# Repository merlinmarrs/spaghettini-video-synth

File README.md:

# spaghettini-video-synth

This simple kit was developed with funding from La Diagonale UP Saclay and the CVEC programme :

"Arduino Coding and Video Synthesis Workshop

Lean to code in C with Arduino, solder and assemble a custom printed-circuit board made in the Fablab, and make your own algorithmically-generated video art!

This workshop is inspired by the improvisational music of Live coding (https://fr.wikipedia.org/wiki/Live_coding) and the burgeoning minimalist Bytebeats movement (https://nightmachines.tv/bytebeats-tutorial).

Our video synthesis kit plugs in to the Arduino (https://www.arduino.cc/), a reprogrammable embedded micro-controller that can interact with the world through code, and uses the VGAX library (https://github.com/smaffer/vgax) to generate funky video.

Meet other creative technologists and sharpen your expertise in computer sciences and electronics soldering!"

**Thank you to Anna Offenwanger for the code !

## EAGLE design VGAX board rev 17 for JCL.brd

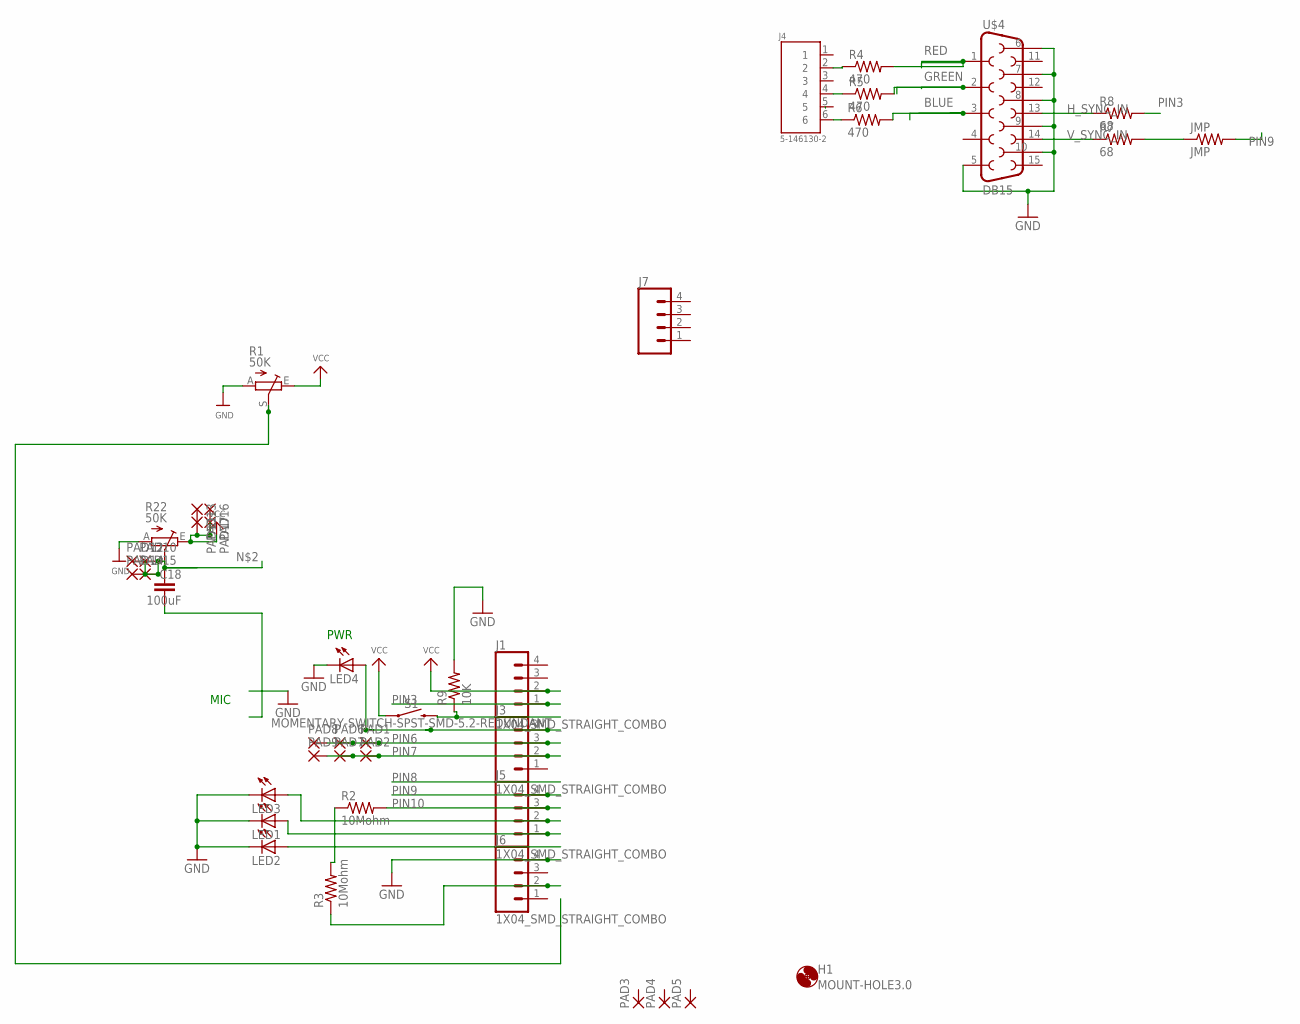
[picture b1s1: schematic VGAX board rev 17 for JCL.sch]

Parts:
C18: 100uF; 1206
H1: MOUNT-HOLE3.0; 3,0
J1, J3, J5, J6, J7: 1X04_SMD_STRAIGHT_COMBO; 1X04_SMD_VERTICAL_COMBO
J4: 5-146130-2
JMP: JMP; M1206
LED1, LED2, LED3, LED4: LEDCHIPLED_1206; CHIPLED_1206
PAD1, PAD2, PAD3, PAD4, PAD5, PAD6, PAD7, PAD8, PAD9, PAD10, PAD11, PAD12, PAD13, PAD14, PAD15, PAD16, PAD17: SMD2; SMD1,27-2,54
R1, R22: 50K; CA9V
R2, R3: 10Mohm; M1206
R4, R5, R6: 470; M1206
R7, R8: 68; M1206
R9: 10K; M1206
S1: MOMENTARY-SWITCH-SPST-SMD-5.2-REDUNDANT; TACTILE_SWITCH_SMD_5.2MM
U$4: DB15

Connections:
BLUE: R6.2, U$4.3
GND: J6.4, LED1.C, LED2.C, LED3.C, LED4.C, R1.A, R9.2, R22.A, U$4.5, U$4.6, U$4.7, U$4.8, U$4.9, U$4.10
GREEN: R5.2, U$4.2
H_SYNC_IN: R8.1, U$4.13
unnamed: JMP.1, R7.2
unnamed: C18.1, PAD10.1, PAD12.1, PAD14.1, PAD15.1, R22.S
unnamed: R2.1, R3.2
unnamed: J5.1, LED1.A
unnamed: J5.2, LED3.A
unnamed: J3.4, LED4.A
unnamed: R9.1, S1.3 (2), S1.4 (2)
unnamed: J4.6, R6.1
unnamed: J4.4, R5.1
unnamed: J4.2, R4.1
PIN3: J1.1, R8.2
PIN6: J3.3, PAD1.1, PAD6.1, PAD8.1
PIN7: J3.2, PAD2.1, PAD7.1, PAD9.1
PIN8: J6.2, R3.1
PIN9: J5.4, JMP.2
PIN10: J5.3, R2.2
RED: R4.2, U$4.1
VCC: J1.2, PAD11.1, PAD16.1, PAD17.1, R1.E, R22.E, S1.1, S1.2 (1)
V_SYNC_IN: R7.1, U$4.14

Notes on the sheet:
PWR
MIC

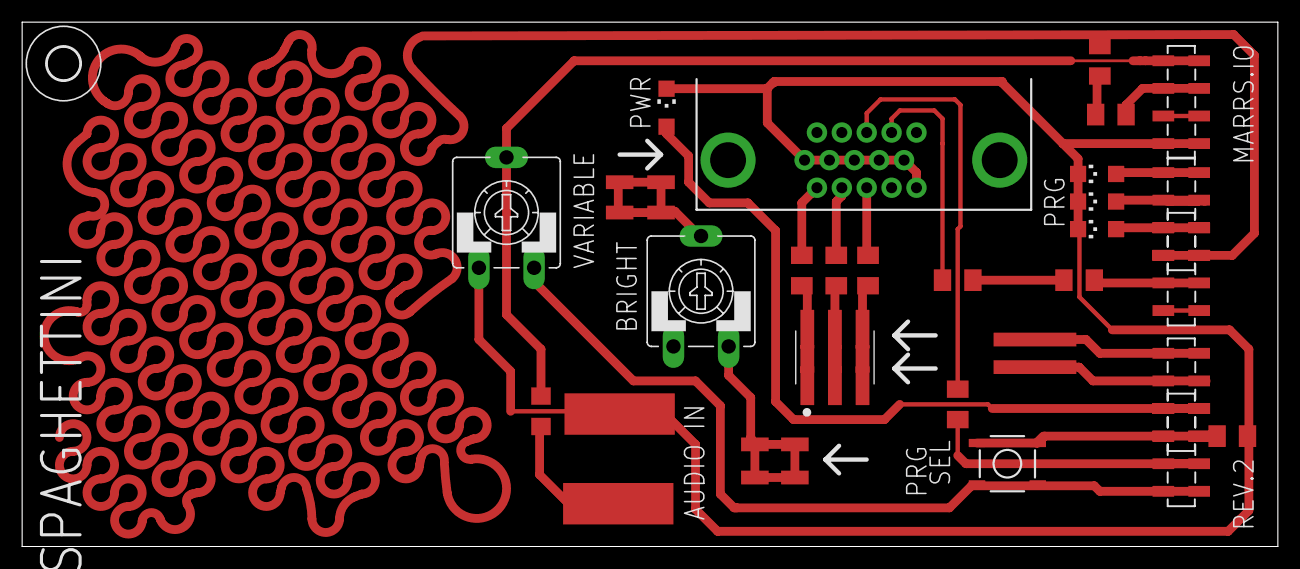
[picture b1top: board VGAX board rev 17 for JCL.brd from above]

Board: 2 copper layers, 115.6 x 48.3 mm, 42 parts (0 on the bottom side), 23 nets.

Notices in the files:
parts and their libraries:
SparkFun-Capacitors: Licensing: Creative Commons ShareAlike 4.0 International - https://creativecommons.org/licenses/by-sa/4.0
microbuilder: This work is placed in the public domain, and may be freely used for commercial and non-commercial work with the following conditions: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
